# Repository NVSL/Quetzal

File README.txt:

### Quetzal

Eagle-Python AutoPlacer 

- How the AutoPlacer is going to check parts that have onBoard and/or offBoard parts??
   -- TODO: if the AutoPlacer has a unlocked part with an off board layer then exit with an error. 

 - TODO: Instead of use half of the size of the part as steps, use a predefined number of steps:(e.g 4)

### Installing 
python setup.py install --record files.txt

## Uninstalling 
cat files.txt | xargs rm -rf

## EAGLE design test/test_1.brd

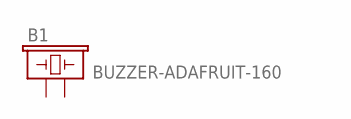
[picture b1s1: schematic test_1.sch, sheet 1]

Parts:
B1: BUZZER-ADAFRUIT-160; BUZZER-12MM-ADAFRUIT-160

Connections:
2_0_BUZZER: B1.- (2); also elsewhere on the board
D3_7_BRAIN: B1.+ (1); also elsewhere on the board

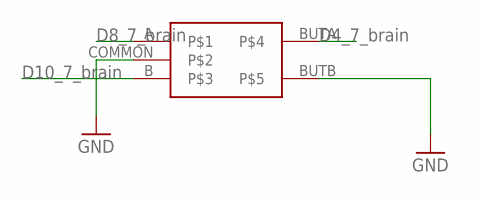
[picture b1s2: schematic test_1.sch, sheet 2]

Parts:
U4: ROTARY-ENCODER-W/BUTTON-ADAFRUIT377

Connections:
2_0_BUZZER: U4.BUTB, U4.COMMON; also elsewhere on the board
D4_7_BRAIN: U4.BUTA; also elsewhere on the board
D8_7_BRAIN: U4.A; also elsewhere on the board
D10_7_BRAIN: U4.B; also elsewhere on the board

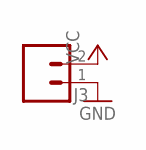
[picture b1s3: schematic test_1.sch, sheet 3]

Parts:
J3: HEADER-0.1IN-2POS-FEMALE; HDRV2W63P254_2X1_508X254H838_HS

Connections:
2_0_BUZZER: J3.1; also elsewhere on the board
+5V_7_BRAIN: J3.2; also elsewhere on the board

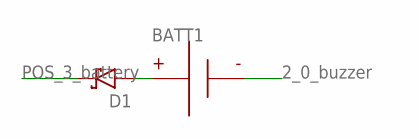
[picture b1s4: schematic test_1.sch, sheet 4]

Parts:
BATT1: BATTERY-9V-VERTICAL; BATTERY_9V_KEYSTONE_968
D1: RESOLVED-DIODE-SCHOTTKY_TH-DO-41-AND-DO-204AL; DIOAD1125W78L520D270_HS; MPN 1N5817

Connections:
2_0_BUZZER: BATT1.N; also elsewhere on the board
unnamed: BATT1.P, D1.A
POS_3_BATTERY: D1.C; also elsewhere on the board

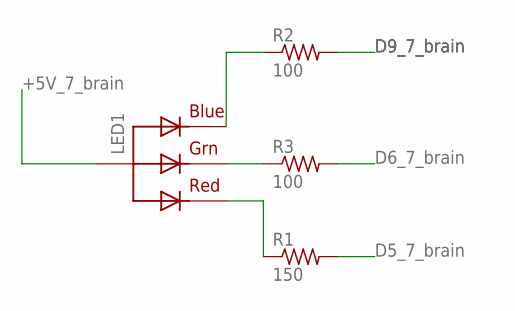
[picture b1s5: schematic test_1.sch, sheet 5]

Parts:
LED1: RGBLED_CA-5MM; LED5MMRGB
R1: 150; RESAD770W45L370D210_HS; MPN CFR-12JB-52-150R
R2, R3: 100; RESAD770W45L370D210_HS; MPN CFR-12JB-52-100R

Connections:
+5V_7_BRAIN: LED1.2 (VCC); also elsewhere on the board
D5_7_BRAIN: R1.2; also elsewhere on the board
D6_7_BRAIN: R3.2; also elsewhere on the board
D9_7_BRAIN: R2.2; also elsewhere on the board
unnamed: LED1.4 (BLUE), R2.1
unnamed: LED1.3 (GREEN), R3.1
unnamed: LED1.1 (RED), R1.1

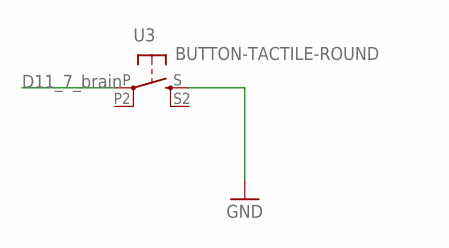
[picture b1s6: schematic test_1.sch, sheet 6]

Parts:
U3: BUTTON-TACTILE-ROUND; BUTTON-TACTILE-ROUND-ADAFRUIT1009

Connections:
2_0_BUZZER: U3.S; also elsewhere on the board
D11_7_BRAIN: U3.P; also elsewhere on the board

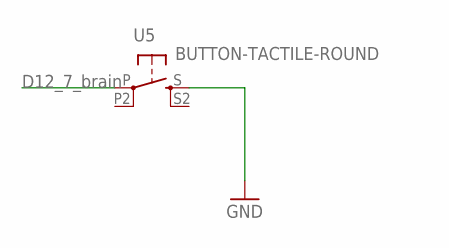
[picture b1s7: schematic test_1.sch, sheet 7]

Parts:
U5: BUTTON-TACTILE-ROUND; BUTTON-TACTILE-ROUND-ADAFRUIT1009

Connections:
2_0_BUZZER: U5.S; also elsewhere on the board
D12_7_BRAIN: U5.P; also elsewhere on the board

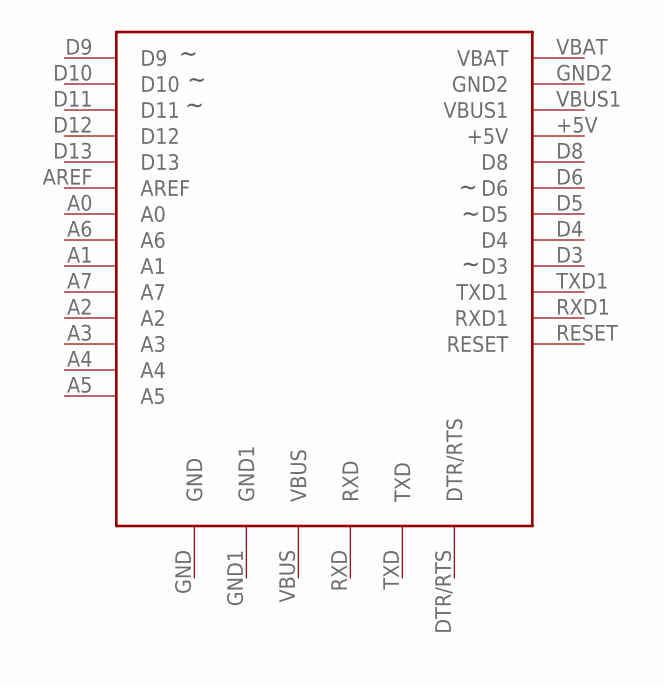
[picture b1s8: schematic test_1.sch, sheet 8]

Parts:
U2: ADAFRUIT-PRO-TRINKET-5V-BOB; ADAFRUIT-PRO-TRINKET-5V

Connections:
2_0_BUZZER: U2.GND, U2.GND1, U2.GND2; also elsewhere on the board
+5V_7_BRAIN: U2.+5V; also elsewhere on the board
A0_7_BRAIN: U2.A0; also elsewhere on the board
A1_7_BRAIN: U2.A1; also elsewhere on the board
A2_7_BRAIN: U2.A2; also elsewhere on the board
A3_7_BRAIN: U2.A3; also elsewhere on the board
A4_7_BRAIN: U2.A4; also elsewhere on the board
A5_7_BRAIN: U2.A5; also elsewhere on the board
A6_7_BRAIN: U2.A6
A7_7_BRAIN: U2.A7
AREF_7_BRAIN: U2.AREF
D3_7_BRAIN: U2.D3; also elsewhere on the board
D4_7_BRAIN: U2.D4; also elsewhere on the board
D5_7_BRAIN: U2.D5; also elsewhere on the board
D6_7_BRAIN: U2.D6; also elsewhere on the board
D8_7_BRAIN: U2.D8; also elsewhere on the board
D9_7_BRAIN: U2.D9; also elsewhere on the board
D10_7_BRAIN: U2.D10; also elsewhere on the board
D11_7_BRAIN: U2.D11; also elsewhere on the board
D12_7_BRAIN: U2.D12; also elsewhere on the board
D13_7_BRAIN: U2.D13; also elsewhere on the board
DTR/RTS_7_BRAIN: U2.DTR/RTS
POS_3_BATTERY: U2.VBAT; also elsewhere on the board
RESET_7_BRAIN: U2.RESET
RXD1_7_BRAIN: U2.RXD1
RXD_7_BRAIN: U2.RXD
TXD1_7_BRAIN: U2.TXD1
TXD_7_BRAIN: U2.TXD
VBUS1_7_BRAIN: U2.VBUS1
VBUS_7_BRAIN: U2.VBUS

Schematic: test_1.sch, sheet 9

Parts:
U1: PROTO-AREA-10X10

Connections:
2_0_BUZZER: U1.P$1 (GND), U1.P$2 (GND), U1.P$3 (GND), U1.P$4 (GND), U1.P$5 (GND), U1.P$6 (GND), U1.P$7 (GND), U1.P$8 (GND), U1.P$9 (GND), U1.P$10 (GND); also elsewhere on the board
+5V_7_BRAIN: U1.P$11 (VCC), U1.P$12 (VCC), U1.P$13 (VCC), U1.P$14 (VCC), U1.P$15 (VCC), U1.P$16 (VCC), U1.P$17 (VCC), U1.P$18 (VCC), U1.P$19 (VCC), U1.P$20 (VCC); also elsewhere on the board

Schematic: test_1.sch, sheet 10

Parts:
J1: HEADER-0.1IN-5POS-FEMALE; HDRV5W63P254_5X1_1270X254H838_HS

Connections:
2_0_BUZZER: J1.1; also elsewhere on the board
+5V_7_BRAIN: J1.2; also elsewhere on the board
A1_7_BRAIN: J1.4; also elsewhere on the board
A2_7_BRAIN: J1.5; also elsewhere on the board
D13_7_BRAIN: J1.3; also elsewhere on the board

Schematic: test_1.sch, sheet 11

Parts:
J4: HEADER-0.1IN-2POS-FEMALE; HDRV2W63P254_2X1_508X254H838_HS

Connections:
2_0_BUZZER: J4.1; also elsewhere on the board
A3_7_BRAIN: J4.2; also elsewhere on the board

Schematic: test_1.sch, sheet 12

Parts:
U6: ADAFRUIT-7SEG-BACKPACK-RED; ADAFRUIT-7SEG-BACKPACK

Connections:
2_0_BUZZER: U6.GND; also elsewhere on the board
+5V_7_BRAIN: U6.VDD; also elsewhere on the board
A4_7_BRAIN: U6.SDA; also elsewhere on the board
A5_7_BRAIN: U6.SCL; also elsewhere on the board

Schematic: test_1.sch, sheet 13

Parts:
J2: HEADER-0.1IN-2POS-FEMALE; HDRV2W63P254_2X1_508X254H838_HS

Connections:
2_0_BUZZER: J2.1; also elsewhere on the board
A0_7_BRAIN: J2.2; also elsewhere on the board

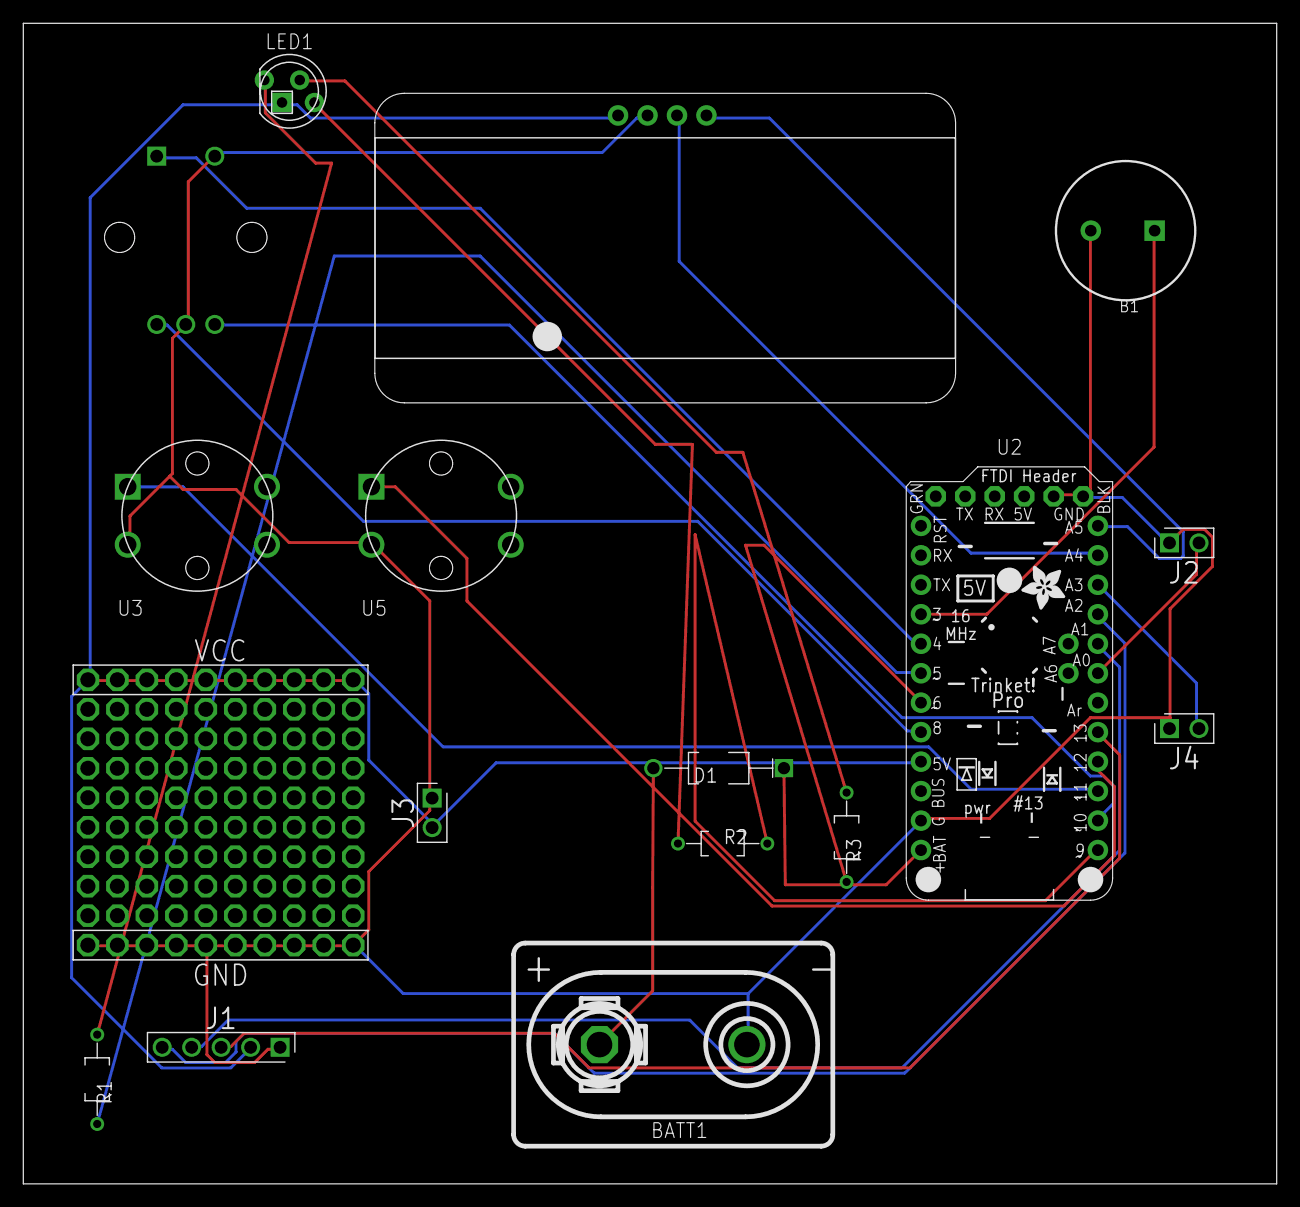
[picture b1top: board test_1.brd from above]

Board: 2 copper layers, 108.0 x 100.0 mm, 18 parts (1 on the bottom side), 23 nets.

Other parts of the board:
LOGO: BUILT_WITH_GADGETRON

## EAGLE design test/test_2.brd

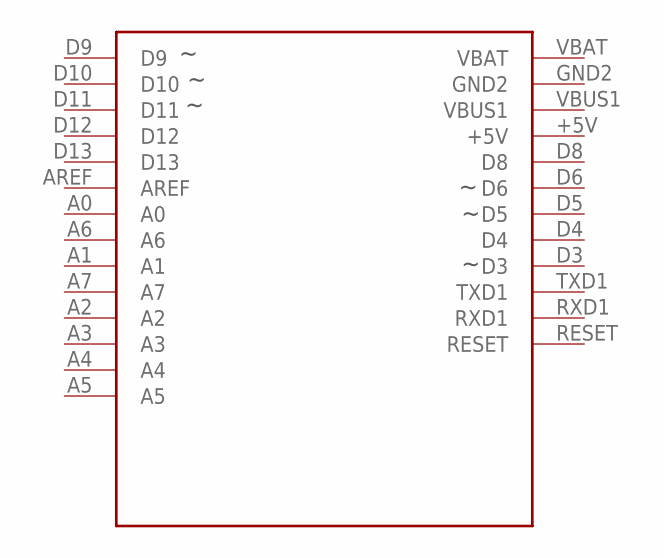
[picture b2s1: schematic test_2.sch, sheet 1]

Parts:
U1_0_brain: ADAFRUIT-PRO-TRINKET-5V-NOFTDI

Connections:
+5V_0_brain: U1_0_brain.+5V; also elsewhere on the board
A0_0_brain: U1_0_brain.A0; also elsewhere on the board
A1_0_brain: U1_0_brain.A1; also elsewhere on the board
A2_0_brain: U1_0_brain.A2; also elsewhere on the board
A3_0_brain: U1_0_brain.A3
A4_0_brain: U1_0_brain.A4; also elsewhere on the board
A5_0_brain: U1_0_brain.A5; also elsewhere on the board
A6_0_brain: U1_0_brain.A6
A7_0_brain: U1_0_brain.A7
AREF_0_brain: U1_0_brain.AREF
D3_0_brain: U1_0_brain.D3; also elsewhere on the board
D4_0_brain: U1_0_brain.D4; also elsewhere on the board
D5_0_brain: U1_0_brain.D5; also elsewhere on the board
D6_0_brain: U1_0_brain.D6; also elsewhere on the board
D8_0_brain: U1_0_brain.D8; also elsewhere on the board
D9_0_brain: U1_0_brain.D9; also elsewhere on the board
D10_0_brain: U1_0_brain.D10; also elsewhere on the board
D11_0_brain: U1_0_brain.D11; also elsewhere on the board
D12_0_brain: U1_0_brain.D12; also elsewhere on the board
D13_0_brain: U1_0_brain.D13; also elsewhere on the board
GND_0_brain: U1_0_brain.GND2; also elsewhere on the board
POS_1_battery: U1_0_brain.VBAT; also elsewhere on the board
RESET_0_brain: U1_0_brain.RESET
RXD1_0_brain: U1_0_brain.RXD1
TXD1_0_brain: U1_0_brain.TXD1
VBUS1_0_brain: U1_0_brain.VBUS1

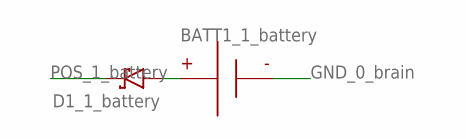
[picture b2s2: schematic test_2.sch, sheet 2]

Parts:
BATT1_1_battery: BATTERY-9V-VERTICAL; BATTERY_9V_KEYSTONE_968
D1_1_battery: RESOLVED-DIODE-SCHOTTKY_TH-DO-41-AND-DO-204AL; DIOAD1125W78L520D270_HS; MPN 1N5817

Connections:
GND_0_brain: BATT1_1_battery.N; also elsewhere on the board
unnamed: BATT1_1_battery.P, D1_1_battery.A
POS_1_battery: D1_1_battery.C; also elsewhere on the board

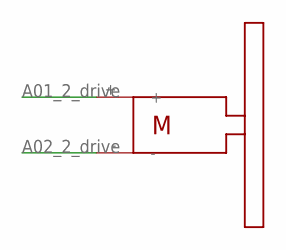
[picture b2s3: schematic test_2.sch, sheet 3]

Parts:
R_2_drive: SOLARBOTICS_GM2SPARKFUN_HOBBY; SPARKFUN_HOBBY_MOTOR

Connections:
A01_2_drive: R_2_drive.+; also elsewhere on the board
A02_2_drive: R_2_drive.-; also elsewhere on the board

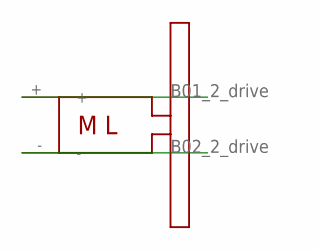
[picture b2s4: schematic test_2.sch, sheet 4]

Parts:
L_2_drive: SOLARBOTICS_GM2_LEFTSPARKFUN_HOBBY; SPARKFUN_HOBBY_MOTOR_LEFT

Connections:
B01_2_drive: L_2_drive.+; also elsewhere on the board
B02_2_drive: L_2_drive.-; also elsewhere on the board

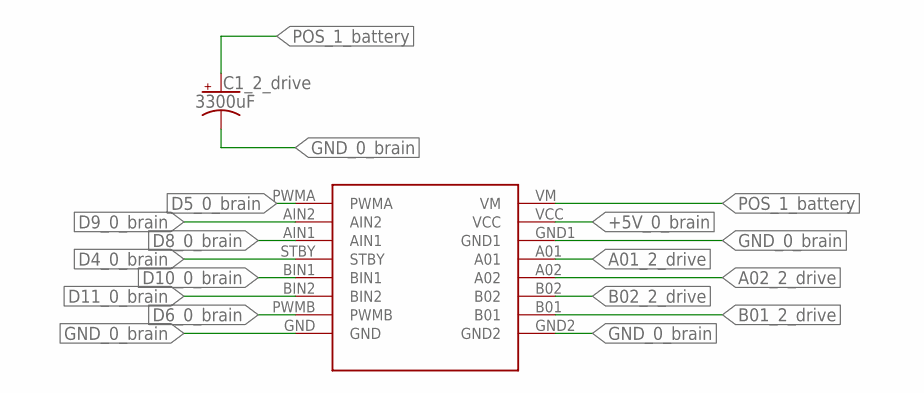
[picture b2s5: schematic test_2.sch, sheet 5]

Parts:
C1_2_drive: 3300uF; CAPPRD750W80D1600H2200P; MPN ECA-1EM332
DRVR_2_drive: SPARKFUN_DUAL_MOTOR_DRIVER-BOB; SPARKFUN_DUAL_MOTOR_DRIVER

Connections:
+5V_0_brain: DRVR_2_drive.VCC; also elsewhere on the board
A01_2_drive: DRVR_2_drive.A01; also elsewhere on the board
A02_2_drive: DRVR_2_drive.A02; also elsewhere on the board
B01_2_drive: DRVR_2_drive.B01; also elsewhere on the board
B02_2_drive: DRVR_2_drive.B02; also elsewhere on the board
D4_0_brain: DRVR_2_drive.STBY; also elsewhere on the board
D5_0_brain: DRVR_2_drive.PWMA; also elsewhere on the board
D6_0_brain: DRVR_2_drive.PWMB; also elsewhere on the board
D8_0_brain: DRVR_2_drive.AIN1; also elsewhere on the board
D9_0_brain: DRVR_2_drive.AIN2; also elsewhere on the board
D10_0_brain: DRVR_2_drive.BIN1; also elsewhere on the board
D11_0_brain: DRVR_2_drive.BIN2; also elsewhere on the board
GND_0_brain: C1_2_drive.2 (-), DRVR_2_drive.GND, DRVR_2_drive.GND1, DRVR_2_drive.GND2; also elsewhere on the board
POS_1_battery: C1_2_drive.1 (+), DRVR_2_drive.VM; also elsewhere on the board

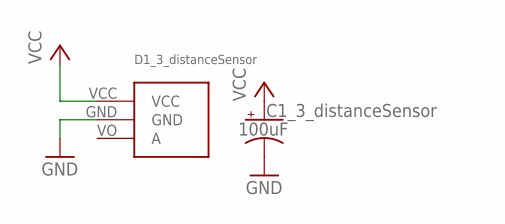
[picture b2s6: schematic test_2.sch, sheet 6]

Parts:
C1_3_distanceSensor: 100uF; CAPPRD250W80D630H1220P; MPN ECA-1EM101
D1_3_distanceSensor: ANALOG_DISTANCE_SENSOR-GLUE; ANALOG_DISTANCE_SENSOR_GLUE_MOUNT

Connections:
+5V_0_brain: C1_3_distanceSensor.1 (+), D1_3_distanceSensor.VCC; also elsewhere on the board
A0_0_brain: D1_3_distanceSensor.VO (A); also elsewhere on the board
GND_0_brain: C1_3_distanceSensor.2 (-), D1_3_distanceSensor.GND; also elsewhere on the board

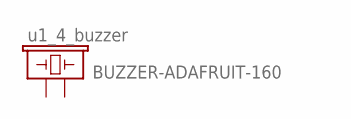
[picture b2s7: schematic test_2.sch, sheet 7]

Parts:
u1_4_buzzer: BUZZER-ADAFRUIT-160; BUZZER-12MM-ADAFRUIT-160

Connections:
D3_0_brain: u1_4_buzzer.+ (1); also elsewhere on the board
GND_0_brain: u1_4_buzzer.- (2); also elsewhere on the board

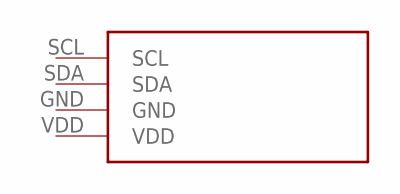
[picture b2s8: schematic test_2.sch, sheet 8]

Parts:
u1_5_display: ADAFRUIT-1.2IN-8X8-LED-BACKPACK-BLUE; ADAFRUIT-1.2IN-8X8-LED-BACKPACK

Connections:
+5V_0_brain: u1_5_display.VDD; also elsewhere on the board
A4_0_brain: u1_5_display.SDA; also elsewhere on the board
A5_0_brain: u1_5_display.SCL; also elsewhere on the board
GND_0_brain: u1_5_display.GND; also elsewhere on the board

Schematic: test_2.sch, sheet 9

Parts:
u1_6_caster: CASTERADAFRUIT-3/4IN; ADAFRUIT-3/4IN-CASTER

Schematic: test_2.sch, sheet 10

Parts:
U$2_7_bump: BUMP_SWITCH-MEDIUM-LEFT; BUMP_SWITCH_OMRON_D2FLA

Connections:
D12_0_brain: U$2_7_bump.A; also elsewhere on the board
GND_0_brain: U$2_7_bump.B; also elsewhere on the board

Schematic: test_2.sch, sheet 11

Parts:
LED1_8_led: LED-5MM-RED; LED5MM
R1_8_led: 330; RESAD770W45L370D210_HS; MPN CFR-12JB-52-330R

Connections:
D13_0_brain: LED1_8_led.A; also elsewhere on the board
GND_0_brain: R1_8_led.2; also elsewhere on the board
unnamed: LED1_8_led.K (C), R1_8_led.1

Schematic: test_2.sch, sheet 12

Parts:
LED1_9_led_2: LED-5MM-BLUE; LED5MM
R1_9_led_2: 330; RESAD770W45L370D210_HS; MPN CFR-12JB-52-330R

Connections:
A2_0_brain: LED1_9_led_2.A; also elsewhere on the board
GND_0_brain: R1_9_led_2.2; also elsewhere on the board
unnamed: LED1_9_led_2.K (C), R1_9_led_2.1

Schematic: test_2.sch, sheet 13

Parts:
C1_10_distanceSensor_2: 100uF; CAPPRD250W80D630H1220P; MPN ECA-1EM101
D1_10_distanceSensor_2: ANALOG_DISTANCE_SENSOR-GLUE; ANALOG_DISTANCE_SENSOR_GLUE_MOUNT

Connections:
+5V_0_brain: C1_10_distanceSensor_2.1 (+), D1_10_distanceSensor_2.VCC; also elsewhere on the board
A1_0_brain: D1_10_distanceSensor_2.VO (A); also elsewhere on the board
GND_0_brain: C1_10_distanceSensor_2.2 (-), D1_10_distanceSensor_2.GND; also elsewhere on the board

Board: 2 copper layers, 20 parts (1 on the bottom side), 25 nets, no tracks yet.

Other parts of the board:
logo: BUILT_WITH_GADGETRON

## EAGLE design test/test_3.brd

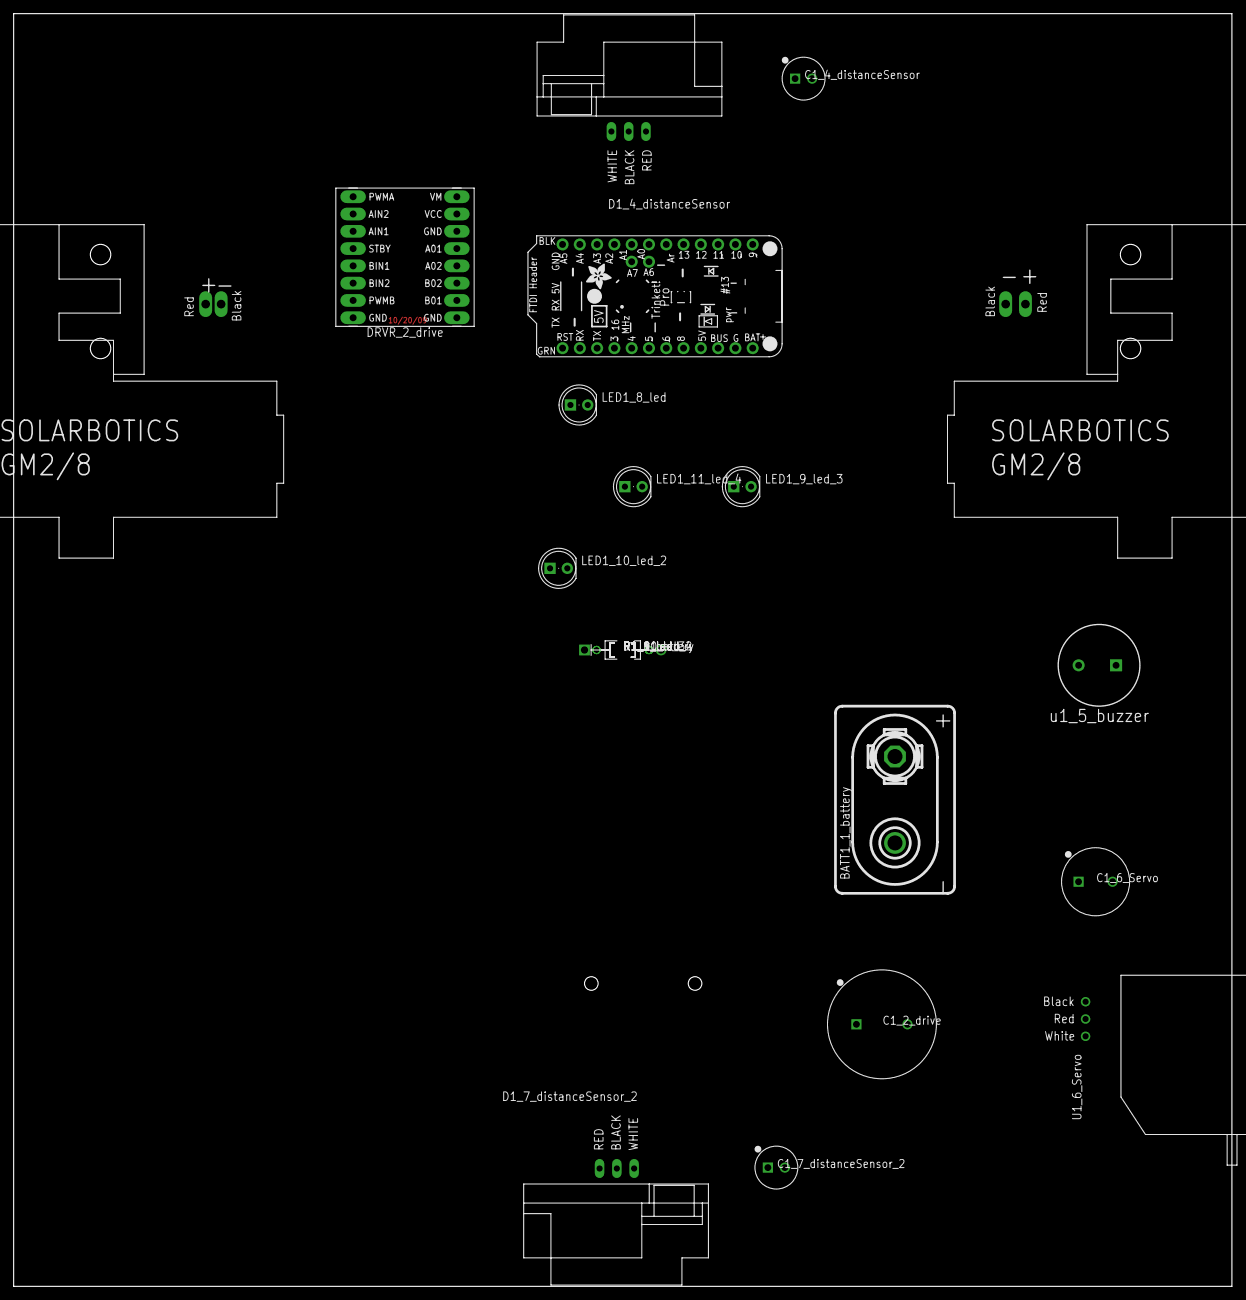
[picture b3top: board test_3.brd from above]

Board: 2 copper layers, 179.0 x 187.0 mm, 24 parts (1 on the bottom side), 27 nets, no tracks yet.

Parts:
BATT1_1_battery: BATTERY-9V-VERTICAL; BATTERY_9V_KEYSTONE_968
C1_2_drive: 3300uF; CAPPRD750W80D1600H2200P
C1_4_distanceSensor, C1_7_distanceSensor_2: 100uF; CAPPRD250W80D630H1220P
C1_6_Servo: 1000uF; CAPPRD500W80D1000H2200P
D1_1_battery: DIOAD1125W78L520D270_HS
D1_4_distanceSensor, D1_7_distanceSensor_2: ANALOG_DISTANCE_SENSOR-GLUE; ANALOG_DISTANCE_SENSOR_GLUE_MOUNT
DRVR_2_drive: SPARKFUN_DUAL_MOTOR_DRIVER-BOB; SPARKFUN_DUAL_MOTOR_DRIVER
LED1_8_led, LED1_9_led_3, LED1_10_led_2, LED1_11_led_4: LED5MM
L_2_drive: SOLARBOTICS_GM2_LEFT; SOLARBOTICS_G2_LEFT
R1_8_led, R1_9_led_3, R1_10_led_2, R1_11_led_4: 330; RESAD770W45L370D210_HS
R_2_drive: SOLARBOTICS_GM2; SOLARBOTICS_G2
U1_0_brain: ADAFRUIT-PRO-TRINKET-5V-NOFTDI
U1_6_Servo: SERVO-MICRO_SIDE_GLUE; SERVO_MICRO_SIDE_GLUE
logo: BUILT_WITH_GADGETRON
u1_3_caster: CASTERADAFRUIT-3/4IN; ADAFRUIT-3/4IN-CASTER
u1_5_buzzer: BUZZER-ADAFRUIT-160; BUZZER-12MM-ADAFRUIT-160

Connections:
+5V_0_brain: C1_4_distanceSensor.1, C1_7_distanceSensor_2.1, D1_4_distanceSensor.VCC, D1_7_distanceSensor_2.VCC, DRVR_2_drive.VCC, U1_0_brain.+5V
A0_0_brain: D1_4_distanceSensor.VO, U1_0_brain.A0
A1_0_brain: D1_7_distanceSensor_2.VO, U1_0_brain.A1
A01_2_drive: DRVR_2_drive.A01, R_2_drive.+
A2_0_brain: LED1_9_led_3.A, U1_0_brain.A2
A02_2_drive: DRVR_2_drive.A02, R_2_drive.-
A3_0_brain: LED1_10_led_2.A, U1_0_brain.A3
A4_0_brain: LED1_11_led_4.A, U1_0_brain.A4
B01_2_drive: DRVR_2_drive.B01, L_2_drive.+
B02_2_drive: DRVR_2_drive.B02, L_2_drive.-
D3_0_brain: U1_0_brain.D3, U1_6_Servo.A1
D4_0_brain: U1_0_brain.D4, u1_5_buzzer.+
D5_0_brain: DRVR_2_drive.PWMA, U1_0_brain.D5
D6_0_brain: DRVR_2_drive.PWMB, U1_0_brain.D6
D8_0_brain: DRVR_2_drive.STBY, U1_0_brain.D8
D9_0_brain: DRVR_2_drive.AIN1, U1_0_brain.D9
D10_0_brain: DRVR_2_drive.AIN2, U1_0_brain.D10
D11_0_brain: DRVR_2_drive.BIN1, U1_0_brain.D11
D12_0_brain: DRVR_2_drive.BIN2, U1_0_brain.D12
D13_0_brain: LED1_8_led.A, U1_0_brain.D13
GND_0_brain: BATT1_1_battery.N, C1_2_drive.2, C1_4_distanceSensor.2, C1_6_Servo.2, C1_7_distanceSensor_2.2, D1_4_distanceSensor.GND, D1_7_distanceSensor_2.GND, DRVR_2_drive.GND, DRVR_2_drive.GND1, DRVR_2_drive.GND2, R1_8_led.2, R1_9_led_3.2, R1_10_led_2.2, R1_11_led_4.2, U1_0_brain.GND2, U1_6_Servo.GND1, u1_5_buzzer.-
unnamed: BATT1_1_battery.P, D1_1_battery.A
unnamed: LED1_8_led.K, R1_8_led.1
unnamed: LED1_9_led_3.K, R1_9_led_3.1
unnamed: LED1_10_led_2.K, R1_10_led_2.1
unnamed: LED1_11_led_4.K, R1_11_led_4.1
POS_1_battery: C1_2_drive.1, C1_6_Servo.1, D1_1_battery.C, DRVR_2_drive.VM, U1_0_brain.VBAT, U1_6_Servo.PWR1

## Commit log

2016-10-31 Initial Quetzal commit
2016-11-01 don't crash on matplotlib on macs. Still run, even if there's nothing to do
2016-11-01 moved matplt imports into functions
2016-11-08 Fixed problem with error placing components from origin
2016-11-09 changed bufer
2016-11-10 changed warning to error
2016-11-12 Adding test unit and function so the autoplacer (quetzal) can run also from object (Swoop.SchematicFile)
2016-11-12 Removing tests direcotry
2016-11-13 Set version
2016-11-18 Fixing bug #1 (adding unittest to makefile)
